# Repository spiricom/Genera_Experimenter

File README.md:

# Genera_H7_rev3
Genera repository for the rev3 boards (summer 2019) STM32H743
test

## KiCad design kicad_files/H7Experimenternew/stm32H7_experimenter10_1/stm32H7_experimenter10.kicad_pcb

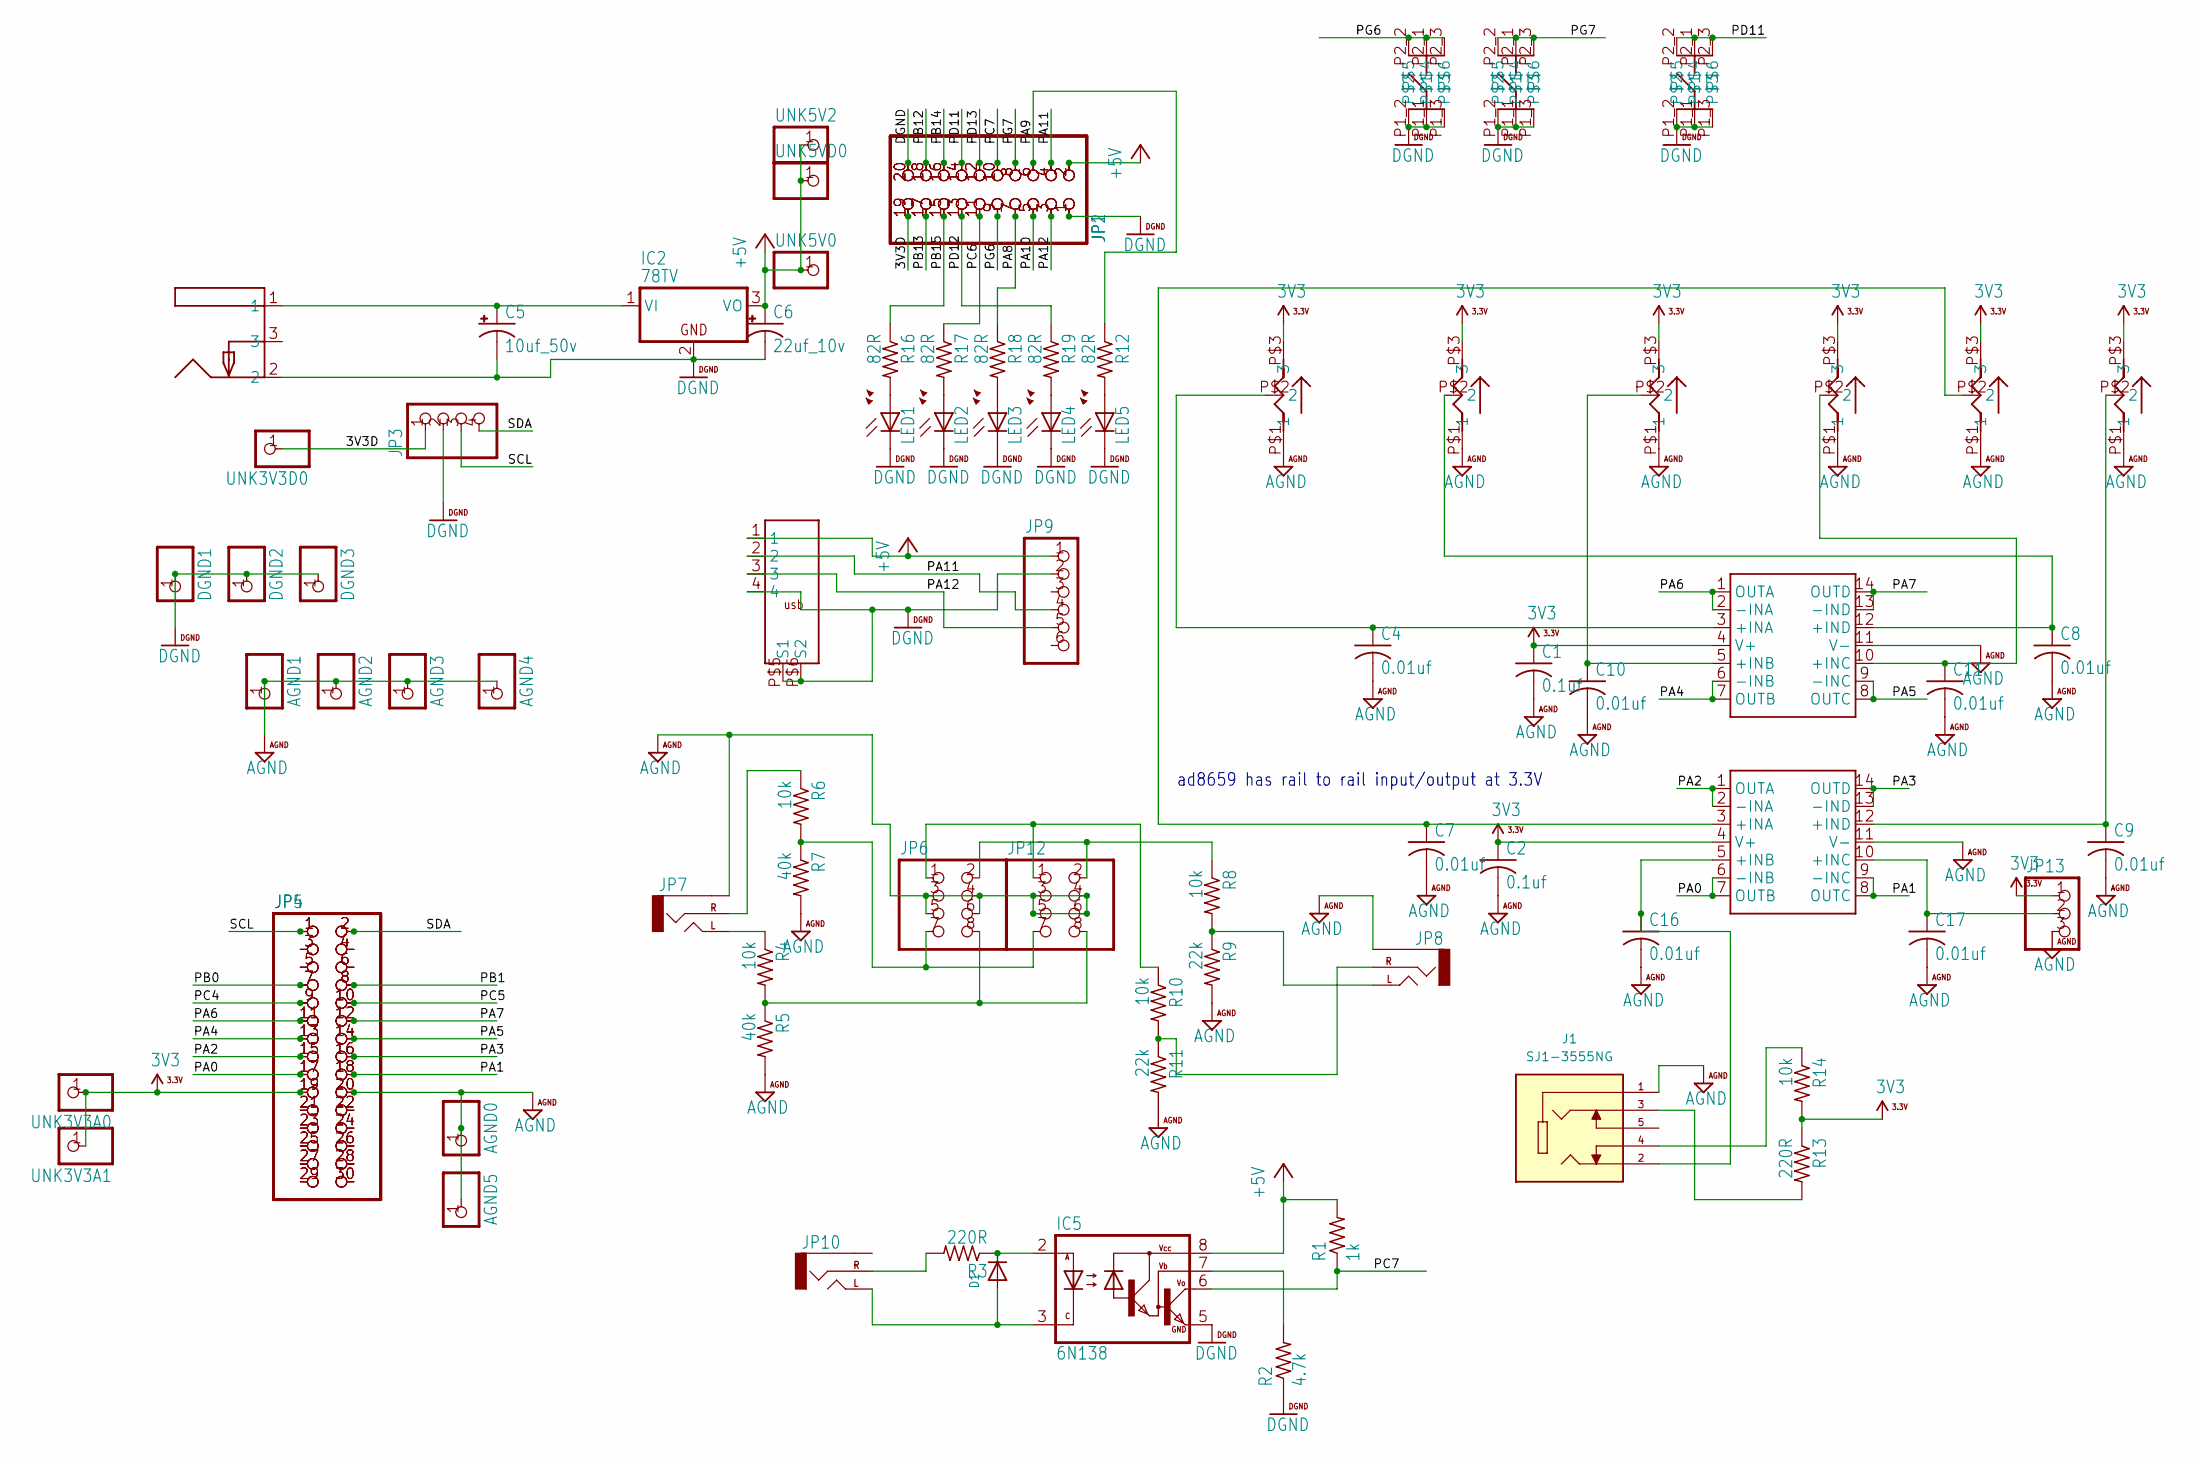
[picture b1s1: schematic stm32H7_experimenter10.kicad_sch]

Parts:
AGND0, AGND1, AGND2, AGND3, AGND4, AGND5: PINHD-1X1; 1X01; PARTNO *DNP
C1, C2: 0.1uf; C025-030X050; PARTNO K104K15X7RF5TL2
C4, C7, C8, C9, C10, C11, C16, C17: 0.01uf; C025-030X050; PARTNO K103K15X7RF5TL2
C5: 10uf_50v; SMC_C; PARTNO 293D106X9035C2TE3
C6: 22uf_10v; SMC_C; PARTNO T491C226K016AT
D1: DIODEDO-1N4148; DO-1N4148; PARTNO 1N4148
DGND1, DGND2, DGND3: PINHD-1X1; 1X01; PARTNO *DNP
IC1, IC3: AD8659; SO14; PARTNO AD8659ARZ-R7
IC2: 78TV; TO220V; PARTNO VX7805-1000
IC5: 6N138; DIL08; PARTNO 6N138
J1: SJ1-3555NG; CUI_SJ1-3555NG; PARTREV 1.05
JP1: PINHD-2X10; 2X10; PARTNO *DNP
JP2: PINHD-2X10; 2X10; PARTNO 67996-120HLF
JP3: PINHD-1X4; 1X04; PARTNO *DNP
JP4: PINHD-2X15; 2X15; PARTNO 67996-130HLF
JP5: PINHD-2X15; 2X15; PARTNO *DNP
JP6: PINHD-2X4; 2X04; PARTNO 67996-108HLF
JP7, JP8, JP10: AUDIO-JACKPTH; AUDIO-JACK; PARTNO SJ1-3525N
JP9: PINHD-1X6; 1X06
JP12: PINHD-2X4; 2X04; PARTNO *DNP
JP13: PINHD-1X3; 1X03; PARTNO *DNP
LED1, LED2, LED3, LED4, LED5: LED3MM; PARTNO 151031SS04000
P1, P2, P3, P4, P5, P6: RK09SONGHUEI; R0904N; PARTNO *
R1: 1k; 0204_5; PARTNO RNMF14FTC1K00
R2: 4.7k; 0204_5; PARTNO RNMF14FTC4K70
R3: 220R; 0204_5; PARTNO RNMF14FTC220R
R4, R6, R8, R10, R14: 10k; 0204_5; PARTNO RNMF14FTC10K0
R5, R7: 40k; 0204_5; PARTNO RNMF14FTC39K0
R9, R11: 22k; 0204_5; PARTNO RNMF14FTC22K0
R12, R18, R19: 82R; 0204_5; PARTNO RNMF14FTC82R0
R13: 220R; 0204_5; PARTNO RNMF14FTC10K0
R16, R17: 82R; 0204V; PARTNO RNMF14FTC82R0
S1, S2, S3: TL52_PLUS; PARTNO TL52AF160Q
U$1: PJ-058AH_PWR_JACK; PJ-058AH
U$3: USB_292303-1; 292303
UNK3V3A0, UNK3V3A1, UNK3V3D0, UNK5V0, UNK5V2, UNK5VD0: PINHD-1X1; 1X01; PARTNO *DNP

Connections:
3V3: C1.1, C2.1, IC1.4 (V+), IC3.4 (V+), JP4.19, JP5.19, JP13.1, P1.P$3 (3), P2.P$3 (3), P3.P$3 (3), P4.P$3 (3), P5.P$3 (3), P6.P$3 (3), R13.1, R14.2, UNK3V3A0.1, UNK3V3A1.1
+5V: C6.+, IC2.3 (VO), IC5.8 (VCC), JP1.2, JP2.2, JP9.1, R1.2, U$3.1, UNK5V0.1, UNK5V2.1, UNK5VD0.1
/3V3D: JP1.19, JP2.19, JP3.1, UNK3V3D0.1
/PA0: IC3.6 (-INB), IC3.7 (OUTB), JP4.17, JP5.17
/PA1: IC3.8 (OUTC), IC3.9 (-INC), JP4.18, JP5.18
/PA2: IC3.1 (OUTA), IC3.2 (-INA), JP4.15, JP5.15
/PA3: IC3.13 (-IND), IC3.14 (OUTD), JP4.16, JP5.16
/PA4: IC1.6 (-INB), IC1.7 (OUTB), JP4.13, JP5.13
/PA5: IC1.8 (OUTC), IC1.9 (-INC), JP4.14, JP5.14
/PA6: IC1.1 (OUTA), IC1.2 (-INA), JP4.11, JP5.11
/PA7: IC1.13 (-IND), IC1.14 (OUTD), JP4.12, JP5.12
/PA8: JP1.7, JP2.7, R18.1
/PA9: JP1.6, JP2.6, R12.1
/PA10: JP1.5, JP2.5
/PA11: JP1.4, JP2.4, JP9.4, U$3.2
/PA12: JP1.3, JP2.3, JP9.5, U$3.3
/PB0: JP4.7, JP5.7
/PB1: JP4.8, JP5.8
/PB12: JP1.18, JP2.18
/PB13: JP1.17, JP2.17
/PB14: JP1.16, JP2.16
/PB15: JP1.15, JP2.15, R16.1
/PC4: JP4.9, JP5.9
/PC5: JP4.10, JP5.10
/PC6: JP1.11, JP2.11, R17.1
/PC7: IC5.6 (VO), JP1.10, JP2.10, R1.1
/PD11: JP1.14, JP2.14, S3.P2_1, S3.P2_2, S3.P2_3
/PD12: JP1.13, JP2.13, R19.1
/PD13: JP1.12, JP2.12
/PG6: JP1.9, JP2.9, S1.P2_1, S1.P2_2, S1.P2_3
/PG7: JP1.8, JP2.8, S2.P2_1, S2.P2_2, S2.P2_3
/SCL: JP3.3, JP4.1, JP5.1
/SDA: JP3.4, JP4.2, JP5.2
AGND: AGND0.1, AGND1.1, AGND2.1, AGND3.1, AGND4.1, AGND5.1, C1.2, C2.2, C4.2, C7.2, C8.2, C9.2, C10.2, C11.2, C16.2, C17.2, IC1.11 (V-), IC3.11 (V-), J1.1, JP4.20, JP5.20, JP6.3, JP6.4, JP6.5, JP6.6, JP7.SLEEVE, JP8.SLEEVE, JP12.3, JP12.4, JP12.5, JP12.6, JP13.3, P1.P$1 (1), P2.P$1 (1), P3.P$1 (1), P4.P$1 (1), P5.P$1 (1), P6.P$1 (1), R5.2, R7.2, R9.2, R11.2
DGND: C5.-, C6.-, DGND1.1, DGND2.1, DGND3.1, IC2.2 (GND), IC5.5 (GND), JP1.1, JP1.20, JP2.1, JP2.20, JP3.2, JP9.2, LED1.K (C), LED2.K (C), LED3.K (C), LED4.K (C), LED5.K (C), R2.1, S1.P1_1, S1.P1_2, S1.P1_3, S2.P1_1, S2.P1_2, S2.P1_3, S3.P1_1, S3.P1_2, S3.P1_3, U$1.2, U$3.4, U$3.P$5 (S1), U$3.P$6 (S2)
unnamed: C4.1, IC1.3 (+INA), P1.P$2 (2)
unnamed: C10.1, IC1.5 (+INB), P3.P$2 (2)
unnamed: C11.1, IC1.10 (+INC), P4.P$2 (2)
unnamed: C8.1, IC1.12 (+IND), P2.P$2 (2)
unnamed: C5.+, IC2.1 (VI), U$1.1
unnamed: C7.1, IC3.3 (+INA), P5.P$2 (2)
unnamed: C16.1, IC3.5 (+INB), J1.2
unnamed: C17.1, IC3.10 (+INC), JP13.2
unnamed: C9.1, IC3.12 (+IND), P6.P$2 (2)
unnamed: D1.C, IC5.2 (A), R3.1
unnamed: D1.A, IC5.3 (C), JP10.TIP (LEFT)
unnamed: IC5.7 (VB), R2.2
unnamed: J1.3, R13.2
unnamed: J1.4, R14.1
unnamed: JP4.3, JP5.3
unnamed: JP4.4, JP5.4
unnamed: JP4.5, JP5.5
unnamed: JP4.6, JP5.6
unnamed: JP4.21, JP5.21
unnamed: JP4.22, JP5.22
unnamed: JP4.23, JP5.23
unnamed: JP4.24, JP5.24
unnamed: JP4.25, JP5.25
unnamed: JP4.26, JP5.26
unnamed: JP4.27, JP5.27
unnamed: JP4.28, JP5.28
unnamed: JP4.29, JP5.29
unnamed: JP4.30, JP5.30
unnamed: JP7.TIP (LEFT), R4.1
unnamed: JP7.RING (RIGHT), R6.1
unnamed: JP8.TIP (LEFT), R8.2, R9.1
unnamed: JP8.RING (RIGHT), R10.2, R11.1
unnamed: JP10.RING (RIGHT), R3.2
unnamed: JP6.1, JP12.1, R10.1
unnamed: JP6.2, JP12.2, R8.1
unnamed: JP6.7, JP12.7, R6.2, R7.1
unnamed: JP6.8, JP12.8, R4.2, R5.1
unnamed: LED1.A, R16.2
unnamed: LED2.A, R17.2
unnamed: LED3.A, R18.2
unnamed: LED4.A, R19.2
unnamed: LED5.A, R12.2

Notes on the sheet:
ad8659 has rail to rail input/output at 3.3V

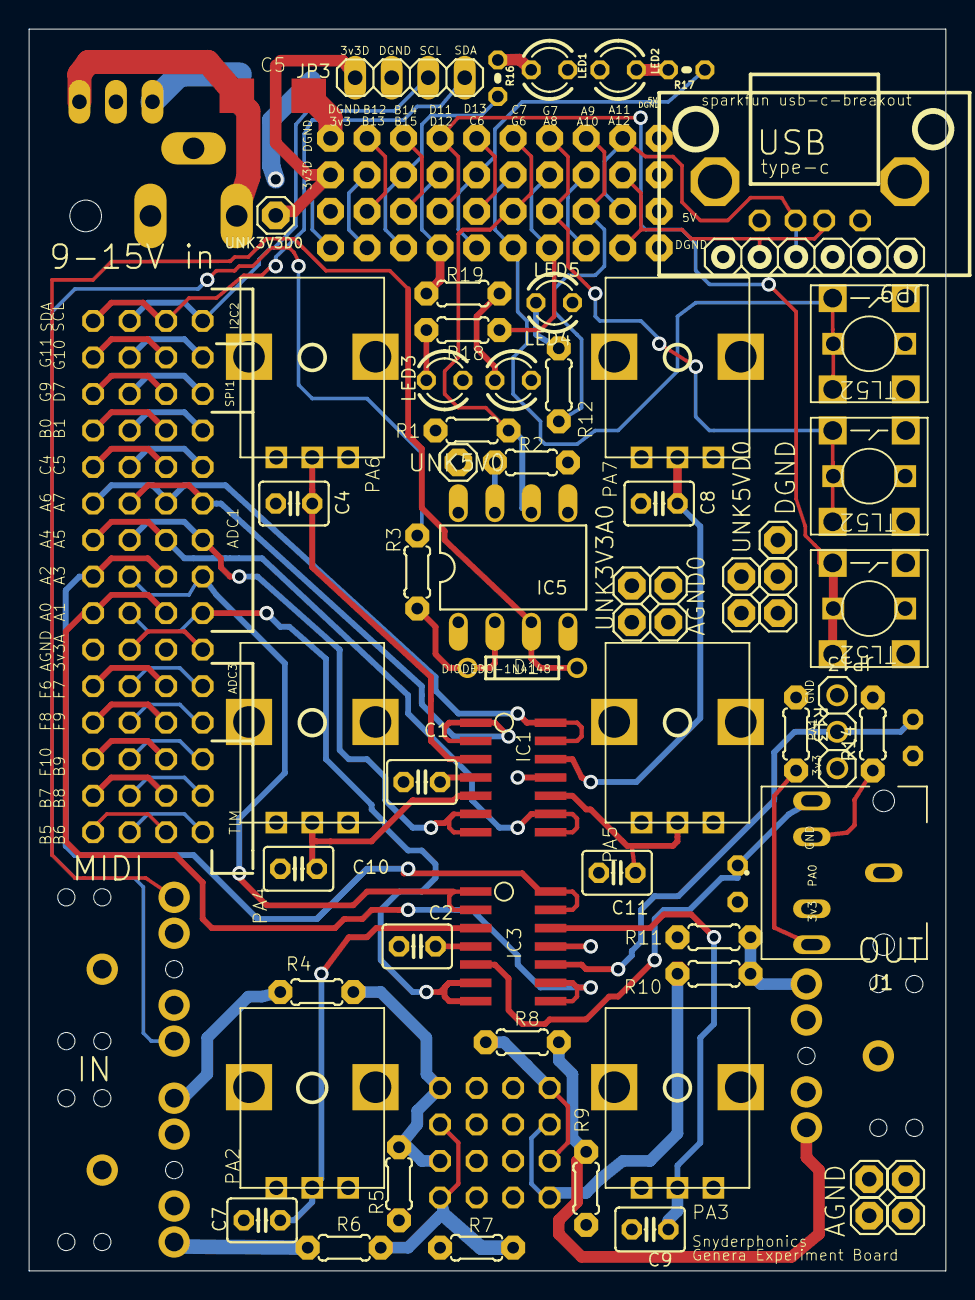
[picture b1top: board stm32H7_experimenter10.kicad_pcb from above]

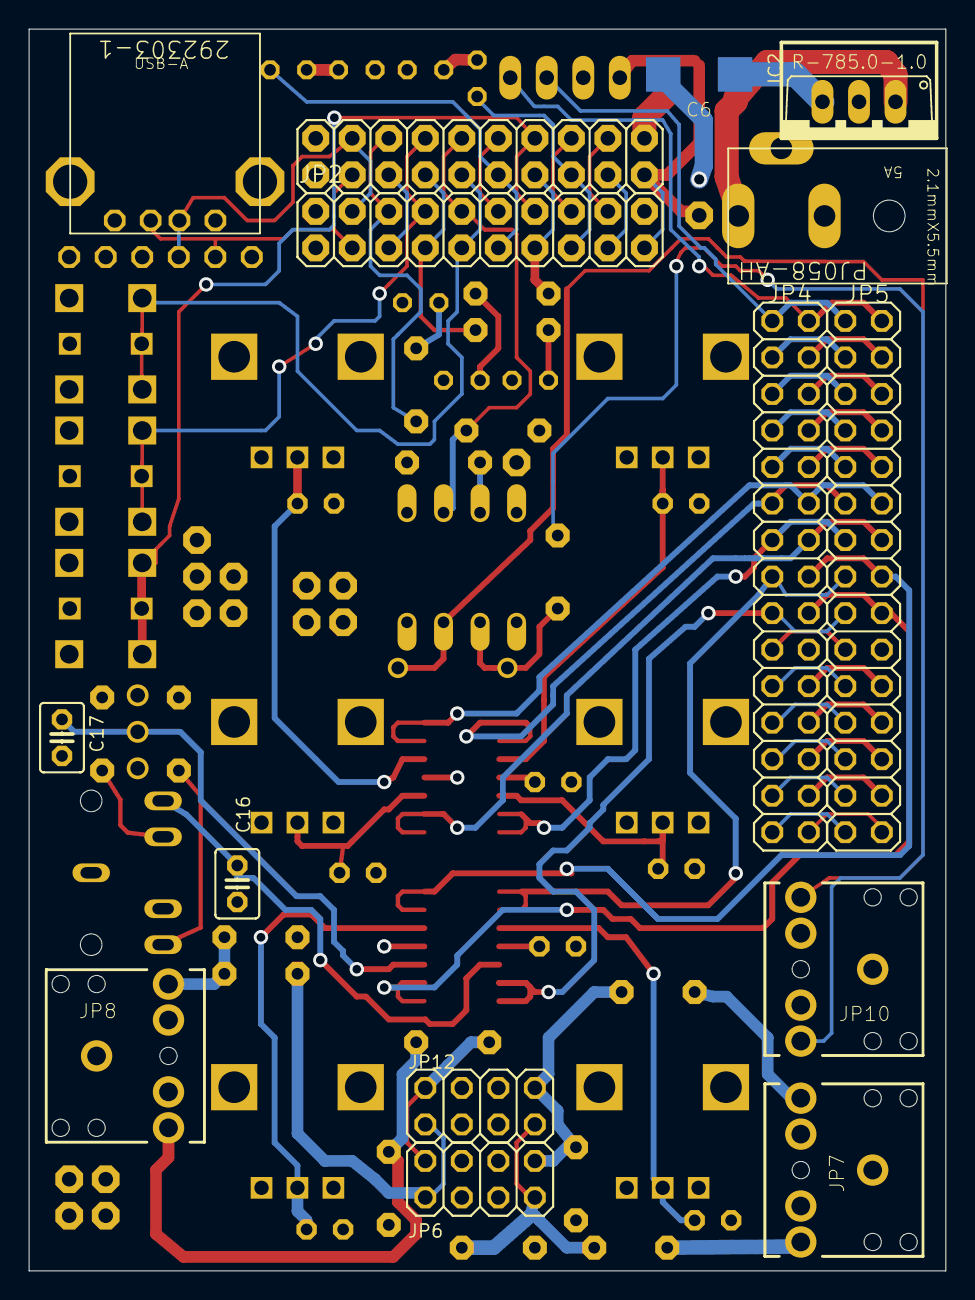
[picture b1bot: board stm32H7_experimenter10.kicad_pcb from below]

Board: 4 copper layers, 63.8 x 86.4 mm, 79 parts (15 on the bottom side), 77 nets.

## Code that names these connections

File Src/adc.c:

/* USER CODE BEGIN Header */
/**
  ******************************************************************************
  * @file    adc.c
  * @brief   This file provides code for the configuration
  *          of the ADC instances.
  ******************************************************************************
  * @attention
  *
  * Copyright (c) 2022 STMicroelectronics.
  * All rights reserved.
  *
  * This software is licensed under terms that can be found in the LICENSE file
  * in the root directory of this software component.
  * If no LICENSE file comes with this software, it is provided AS-IS.
  *
  ******************************************************************************
  */
/* USER CODE END Header */
/* Includes ------------------------------------------------------------------*/
#include "adc.h"

/* USER CODE BEGIN 0 */

/* USER CODE END 0 */

ADC_HandleTypeDef hadc1;
DMA_HandleTypeDef hdma_adc1;

/* ADC1 init function */
void MX_ADC1_Init(void)
{

  /* USER CODE BEGIN ADC1_Init 0 */

  /* USER CODE END ADC1_Init 0 */

  ADC_MultiModeTypeDef multimode = {0};
  ADC_ChannelConfTypeDef sConfig = {0};

  /* USER CODE BEGIN ADC1_Init 1 */

  /* USER CODE END ADC1_Init 1 */

  /** Common config
  */
  hadc1.Instance = ADC1;
  hadc1.Init.ClockPrescaler = ADC_CLOCK_ASYNC_DIV4;
  hadc1.Init.Resolution = ADC_RESOLUTION_16B;
  hadc1.Init.ScanConvMode = ADC_SCAN_ENABLE;
  hadc1.Init.EOCSelection = ADC_EOC_SEQ_CONV;
  hadc1.Init.LowPowerAutoWait = DISABLE;
  hadc1.Init.ContinuousConvMode = ENABLE;
  hadc1.Init.NbrOfConversion = 6;
  hadc1.Init.DiscontinuousConvMode = DISABLE;
  hadc1.Init.ExternalTrigConv = ADC_SOFTWARE_START;
  hadc1.Init.ExternalTrigConvEdge = ADC_EXTERNALTRIGCONVEDGE_NONE;
  hadc1.Init.ConversionDataManagement = ADC_CONVERSIONDATA_DMA_CIRCULAR;
  hadc1.Init.Overrun = ADC_OVR_DATA_PRESERVED;
  hadc1.Init.LeftBitShift = ADC_LEFTBITSHIFT_NONE;
  hadc1.Init.OversamplingMode = ENABLE;
  hadc1.Init.Oversampling.Ratio = 64;
  hadc1.Init.Oversampling.RightBitShift = ADC_RIGHTBITSHIFT_6;
  hadc1.Init.Oversampling.TriggeredMode = ADC_TRIGGEREDMODE_SINGLE_TRIGGER;
  hadc1.Init.Oversampling.OversamplingStopReset = ADC_REGOVERSAMPLING_CONTINUED_MODE;
  if (HAL_ADC_Init(&hadc1) != HAL_OK)
  {
    Error_Handler();
  }

  /** Configure the ADC multi-mode
  */
  multimode.Mode = ADC_MODE_INDEPENDENT;
  if (HAL_ADCEx_MultiModeConfigChannel(&hadc1, &multimode) != HAL_OK)
  {
    Error_Handler();
  }

  /** Configure Regular Channel
  */
  sConfig.Channel = ADC_CHANNEL_7;
  sConfig.Rank = ADC_REGULAR_RANK_1;
  sConfig.SamplingTime = ADC_SAMPLETIME_64CYCLES_5;
  sConfig.SingleDiff = ADC_SINGLE_ENDED;
  sConfig.OffsetNumber = ADC_OFFSET_NONE;
  sConfig.Offset = 0;
  sConfig.OffsetSignedSaturation = DISABLE;
  if (HAL_ADC_ConfigChannel(&hadc1, &sConfig) != HAL_OK)
  {
    Error_Handler();
  }

  /** Configure Regular Channel
  */
  sConfig.Channel = ADC_CHANNEL_3;
  sConfig.Rank = ADC_REGULAR_RANK_2;
  if (HAL_ADC_ConfigChannel(&hadc1, &sConfig) != HAL_OK)
  {
    Error_Handler();
  }

  /** Configure Regular Channel
  */
  sConfig.Channel = ADC_CHANNEL_19;
  sConfig.Rank = ADC_REGULAR_RANK_3;
  if (HAL_ADC_ConfigChannel(&hadc1, &sConfig) != HAL_OK)
  {
    Error_Handler();
  }

  /** Configure Regular Channel
  */
  sConfig.Channel = ADC_CHANNEL_18;
  sConfig.Rank = ADC_REGULAR_RANK_4;
  if (HAL_ADC_ConfigChannel(&hadc1, &sConfig) != HAL_OK)
  {
    Error_Handler();
  }

  /** Configure Regular Channel
  */
  sConfig.Channel = ADC_CHANNEL_15;
  sConfig.Rank = ADC_REGULAR_RANK_5;
  if (HAL_ADC_ConfigChannel(&hadc1, &sConfig) != HAL_OK)
  {
    Error_Handler();
  }

  /** Configure Regular Channel
  */
  sConfig.Channel = ADC_CHANNEL_14;
  sConfig.Rank = ADC_REGULAR_RANK_6;
  if (HAL_ADC_ConfigChannel(&hadc1, &sConfig) != HAL_OK)
  {
    Error_Handler();
  }
  /* USER CODE BEGIN ADC1_Init 2 */

  /* USER CODE END ADC1_Init 2 */

}

void HAL_ADC_MspInit(ADC_HandleTypeDef* adcHandle)
{

  GPIO_InitTypeDef GPIO_InitStruct = {0};
  HAL_DMA_MuxSyncConfigTypeDef pSyncConfig= {0};
  if(adcHandle->Instance==ADC1)
  {
  /* USER CODE BEGIN ADC1_MspInit 0 */

  /* USER CODE END ADC1_MspInit 0 */
    /* ADC1 clock enable */
    __HAL_RCC_ADC12_CLK_ENABLE();

    __HAL_RCC_GPIOA_CLK_ENABLE();
    /**ADC1 GPIO Configuration
    PA0     ------> ADC1_INP16
    PA1     ------> ADC1_INN16
    PA1     ------> ADC1_INP17
    PA2     ------> ADC1_INP14
    PA3     ------> ADC1_INP15
    PA4     ------> ADC1_INP18
    PA5     ------> ADC1_INP19
    PA6     ------> ADC1_INP3
    PA7     ------> ADC1_INP7
    */
    GPIO_InitStruct.Pin = GPIO_PIN_0|GPIO_PIN_1|GPIO_PIN_2|GPIO_PIN_3
                          |GPIO_PIN_4|GPIO_PIN_5|GPIO_PIN_6|GPIO_PIN_7;
    GPIO_InitStruct.Mode = GPIO_MODE_ANALOG;
    GPIO_InitStruct.Pull = GPIO_NOPULL;
    HAL_GPIO_Init(GPIOA, &GPIO_InitStruct);

    /* ADC1 DMA Init */
    /* ADC1 Init */
    hdma_adc1.Instance = DMA2_Stream0;
    hdma_adc1.Init.Request = DMA_REQUEST_ADC1;
    hdma_adc1.Init.Direction = DMA_PERIPH_TO_MEMORY;
    hdma_adc1.Init.PeriphInc = DMA_PINC_DISABLE;
    hdma_adc1.Init.MemInc = DMA_MINC_ENABLE;
    hdma_adc1.Init.PeriphDataAlignment = DMA_PDATAALIGN_HALFWORD;
    hdma_adc1.Init.MemDataAlignment = DMA_MDATAALIGN_HALFWORD;
    hdma_adc1.Init.Mode = DMA_CIRCULAR;
    hdma_adc1.Init.Priority = DMA_PRIORITY_HIGH;
    hdma_adc1.Init.FIFOMode = DMA_FIFOMODE_ENABLE;
    hdma_adc1.Init.FIFOThreshold = DMA_FIFO_THRESHOLD_1QUARTERFULL;
    hdma_adc1.Init.MemBurst = DMA_MBURST_SINGLE;
    hdma_adc1.Init.PeriphBurst = DMA_PBURST_SINGLE;
    if (HAL_DMA_Init(&hdma_adc1) != HAL_OK)
    {
      Error_Handler();
    }

    pSyncConfig.SyncSignalID = HAL_DMAMUX1_SYNC_EXTI0;
    pSyncConfig.SyncPolarity = HAL_DMAMUX_SYNC_RISING;
    pSyncConfig.SyncEnable = DISABLE;
    pSyncConfig.EventEnable = ENABLE;
    pSyncConfig.RequestNumber = 1;
    if (HAL_DMAEx_ConfigMuxSync(&hdma_adc1, &pSyncConfig) != HAL_OK)
    {
      Error_Handler();
    }

    __HAL_LINKDMA(adcHandle,DMA_Handle,hdma_adc1);

    /* ADC1 interrupt Init */
    HAL_NVIC_SetPriority(ADC_IRQn, 5, 0);
    HAL_NVIC_EnableIRQ(ADC_IRQn);
  /* USER CODE BEGIN ADC1_MspInit 1 */

  /* USER CODE END ADC1_MspInit 1 */
  }
}

void HAL_ADC_MspDeInit(ADC_HandleTypeDef* adcHandle)
{

  if(adcHandle->Instance==ADC1)
  {
  /* USER CODE BEGIN ADC1_MspDeInit 0 */

  /* USER CODE END ADC1_MspDeInit 0 */
    /* Peripheral clock disable */
    __HAL_RCC_ADC12_CLK_DISABLE();

    /**ADC1 GPIO Configuration
    PA0     ------> ADC1_INP16
    PA1     ------> ADC1_INN16
    PA1     ------> ADC1_INP17
    PA2     ------> ADC1_INP14
    PA3     ------> ADC1_INP15
    PA4     ------> ADC1_INP18
    PA5     ------> ADC1_INP19
    PA6     ------> ADC1_INP3
    PA7     ------> ADC1_INP7
    */
    HAL_GPIO_DeInit(GPIOA, GPIO_PIN_0|GPIO_PIN_1|GPIO_PIN_2|GPIO_PIN_3
                          |GPIO_PIN_4|GPIO_PIN_5|GPIO_PIN_6|GPIO_PIN_7);

    /* ADC1 DMA DeInit */
    HAL_DMA_DeInit(adcHandle->DMA_Handle);

    /* ADC1 interrupt Deinit */
    HAL_NVIC_DisableIRQ(ADC_IRQn);
  /* USER CODE BEGIN ADC1_MspDeInit 1 */

  /* USER CODE END ADC1_MspDeInit 1 */
  }
}

/* USER CODE BEGIN 1 */

/* USER CODE END 1 */

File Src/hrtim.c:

/* USER CODE BEGIN Header */
/**
  ******************************************************************************
  * @file    hrtim.c
  * @brief   This file provides code for the configuration
  *          of the HRTIM instances.
  ******************************************************************************
  * @attention
  *
  * Copyright (c) 2026 STMicroelectronics.
  * All rights reserved.
  *
  * This software is licensed under terms that can be found in the LICENSE file
  * in the root directory of this software component.
  * If no LICENSE file comes with this software, it is provided AS-IS.
  *
  ******************************************************************************
  */
/* USER CODE END Header */
/* Includes ------------------------------------------------------------------*/
#include "hrtim.h"

/* USER CODE BEGIN 0 */

/* USER CODE END 0 */

HRTIM_HandleTypeDef hhrtim;

/* HRTIM init function */
void MX_HRTIM_Init(void)
{

  /* USER CODE BEGIN HRTIM_Init 0 */

  /* USER CODE END HRTIM_Init 0 */

  HRTIM_TimeBaseCfgTypeDef pTimeBaseCfg = {0};
  HRTIM_SimplePWMChannelCfgTypeDef pSimplePWMChannelCfg = {0};

  /* USER CODE BEGIN HRTIM_Init 1 */

  /* USER CODE END HRTIM_Init 1 */
  hhrtim.Instance = HRTIM1;
  hhrtim.Init.HRTIMInterruptResquests = HRTIM_IT_NONE;
  hhrtim.Init.SyncOptions = HRTIM_SYNCOPTION_NONE;
  if (HAL_HRTIM_Init(&hhrtim) != HAL_OK)
  {
    Error_Handler();
  }
  pTimeBaseCfg.Period = 0x3fff;
  pTimeBaseCfg.RepetitionCounter = 0x00;
  pTimeBaseCfg.PrescalerRatio = HRTIM_PRESCALERRATIO_DIV1;
  pTimeBaseCfg.Mode = HRTIM_MODE_CONTINUOUS;
  if (HAL_HRTIM_TimeBaseConfig(&hhrtim, HRTIM_TIMERINDEX_TIMER_B, &pTimeBaseCfg) != HAL_OK)
  {
    Error_Handler();
  }
  pSimplePWMChannelCfg.Pulse = 0x7ff;
  pSimplePWMChannelCfg.Polarity = HRTIM_OUTPUTPOLARITY_HIGH;
  pSimplePWMChannelCfg.IdleLevel = HRTIM_OUTPUTIDLELEVEL_INACTIVE;
  if (HAL_HRTIM_SimplePWMChannelConfig(&hhrtim, HRTIM_TIMERINDEX_TIMER_B, HRTIM_OUTPUT_TB2, &pSimplePWMChannelCfg) != HAL_OK)
  {
    Error_Handler();
  }
  if (HAL_HRTIM_TimeBaseConfig(&hhrtim, HRTIM_TIMERINDEX_TIMER_C, &pTimeBaseCfg) != HAL_OK)
  {
    Error_Handler();
  }
  if (HAL_HRTIM_SimplePWMChannelConfig(&hhrtim, HRTIM_TIMERINDEX_TIMER_C, HRTIM_OUTPUT_TC1, &pSimplePWMChannelCfg) != HAL_OK)
  {
    Error_Handler();
  }
  if (HAL_HRTIM_SimplePWMChannelConfig(&hhrtim, HRTIM_TIMERINDEX_TIMER_C, HRTIM_OUTPUT_TC2, &pSimplePWMChannelCfg) != HAL_OK)
  {
    Error_Handler();
  }
  if (HAL_HRTIM_TimeBaseConfig(&hhrtim, HRTIM_TIMERINDEX_TIMER_D, &pTimeBaseCfg) != HAL_OK)
  {
    Error_Handler();
  }
  if (HAL_HRTIM_SimplePWMChannelConfig(&hhrtim, HRTIM_TIMERINDEX_TIMER_D, HRTIM_OUTPUT_TD1, &pSimplePWMChannelCfg) != HAL_OK)
  {
    Error_Handler();
  }
  if (HAL_HRTIM_SimplePWMChannelConfig(&hhrtim, HRTIM_TIMERINDEX_TIMER_D, HRTIM_OUTPUT_TD2, &pSimplePWMChannelCfg) != HAL_OK)
  {
    Error_Handler();
  }
  if (HAL_HRTIM_TimeBaseConfig(&hhrtim, HRTIM_TIMERINDEX_TIMER_E, &pTimeBaseCfg) != HAL_OK)
  {
    Error_Handler();
  }
  if (HAL_HRTIM_SimplePWMChannelConfig(&hhrtim, HRTIM_TIMERINDEX_TIMER_E, HRTIM_OUTPUT_TE2, &pSimplePWMChannelCfg) != HAL_OK)
  {
    Error_Handler();
  }
  /* USER CODE BEGIN HRTIM_Init 2 */

  /* USER CODE END HRTIM_Init 2 */
  HAL_HRTIM_MspPostInit(&hhrtim);

}

void HAL_HRTIM_MspInit(HRTIM_HandleTypeDef* hrtimHandle)
{

  RCC_PeriphCLKInitTypeDef PeriphClkInitStruct = {0};
  if(hrtimHandle->Instance==HRTIM1)
  {
  /* USER CODE BEGIN HRTIM1_MspInit 0 */

  /* USER CODE END HRTIM1_MspInit 0 */

  /** Initializes the peripherals clock
  */
    PeriphClkInitStruct.PeriphClockSelection = RCC_PERIPHCLK_HRTIM1;
    PeriphClkInitStruct.Hrtim1ClockSelection = RCC_HRTIM1CLK_CPUCLK;
    if (HAL_RCCEx_PeriphCLKConfig(&PeriphClkInitStruct) != HAL_OK)
    {
      Error_Handler();
    }

    /* HRTIM1 clock enable */
    __HAL_RCC_HRTIM1_CLK_ENABLE();
  /* USER CODE BEGIN HRTIM1_MspInit 1 */

  /* USER CODE END HRTIM1_MspInit 1 */
  }
}

void HAL_HRTIM_MspPostInit(HRTIM_HandleTypeDef* hrtimHandle)
{

  GPIO_InitTypeDef GPIO_InitStruct = {0};
  if(hrtimHandle->Instance==HRTIM1)
  {
  /* USER CODE BEGIN HRTIM1_MspPostInit 0 */

  /* USER CODE END HRTIM1_MspPostInit 0 */

    __HAL_RCC_GPIOG_CLK_ENABLE();
    __HAL_RCC_GPIOA_CLK_ENABLE();
    /**HRTIM GPIO Configuration
    PG7     ------> HRTIM_CHE2
    PA8     ------> HRTIM_CHB2
    PA9     ------> HRTIM_CHC1
    PA10     ------> HRTIM_CHC2
    PA11     ------> HRTIM_CHD1
    PA12     ------> HRTIM_CHD2
    */
    GPIO_InitStruct.Pin = GPIO_PIN_7;
    GPIO_InitStruct.Mode = GPIO_MODE_AF_PP;
    GPIO_InitStruct.Pull = GPIO_NOPULL;
    GPIO_InitStruct.Speed = GPIO_SPEED_FREQ_LOW;
    GPIO_InitStruct.Alternate = GPIO_AF2_HRTIM1;
    HAL_GPIO_Init(GPIOG, &GPIO_InitStruct);

    GPIO_InitStruct.Pin = GPIO_PIN_8|GPIO_PIN_9|GPIO_PIN_10|GPIO_PIN_11
                          |GPIO_PIN_12;
    GPIO_InitStruct.Mode = GPIO_MODE_AF_PP;
    GPIO_InitStruct.Pull = GPIO_NOPULL;
    GPIO_InitStruct.Speed = GPIO_SPEED_FREQ_LOW;
    GPIO_InitStruct.Alternate = GPIO_AF2_HRTIM1;
    HAL_GPIO_Init(GPIOA, &GPIO_InitStruct);

  /* USER CODE BEGIN HRTIM1_MspPostInit 1 */

  /* USER CODE END HRTIM1_MspPostInit 1 */
  }

}

void HAL_HRTIM_MspDeInit(HRTIM_HandleTypeDef* hrtimHandle)
{

  if(hrtimHandle->Instance==HRTIM1)
  {
  /* USER CODE BEGIN HRTIM1_MspDeInit 0 */

  /* USER CODE END HRTIM1_MspDeInit 0 */
    /* Peripheral clock disable */
    __HAL_RCC_HRTIM1_CLK_DISABLE();
  /* USER CODE BEGIN HRTIM1_MspDeInit 1 */

  /* USER CODE END HRTIM1_MspDeInit 1 */
  }
}

/* USER CODE BEGIN 1 */

/* USER CODE END 1 */

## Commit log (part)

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2020-02-20 updating
2020-03-07 fixed issues with build and broken sw4stm config file
2020-03-07 added mempools to example
2020-03-07 fixed linker file to allow for SDRAM access
2020-03-21 added SPI
2020-03-22 removed unnecessary HAL peripherals, added string fret measurements roughly
2020-03-24 working electrobass makes sound but needs better attack detection
2020-03-26 working attack detector
2020-03-26 slight tweak to reduce mistriggers
2020-04-20 electrobass update;
2020-04-20 added usb midi functionality"
2020-04-23 added vadim zavalishin filters to have high and low shelf, and also saturation
2020-04-23 finished mackie-style eq example using the new Vadim Zavalashin filters. It works! Overloads when boosting highs, but thats probably because the source is white noise with more energy in the upper fr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
2020-04-23 filter test example
2020-06-20 got 3 ADC input channels syncronized with audio frame and samples. They can be used as audio inputs without distortion
2020-06-21 working example that detects which sensor was closest to strike based on oversampled time difference
2020-06-23 migrated to cubeide
2020-06-23 migrated to cubeide and fixed some things
2020-06-25 testing
2020-07-09 edited lots of things, somewht working pluck detection in adc callback, simple monophonic handling
2020-07-10 decent attack detection, currently trying to work on logging to SD card
2020-07-11 got data logging working up to about 50000 bytes. Need to extend beyond that by buffering and sending in chunks or by using SDRAM as temporary storage.
2020-07-27 code to record full sensor data from the electrobass and store it to an SD card for analysis
2020-08-25 updating electrobass
2020-08-30 simple distortion 192k
2020-08-31 distortion 192k example
2020-08-31 cleaned up cycle counter cruft
2020-08-31 updated code to reflect new LEAF changes
2020-08-31 added comment to explain interface;
2020-08-31 newer version with 2X oversampling of all saturation and no saturation in filters
2020-08-31 adjusted ranges of controls for better filtering
2020-08-31 moved comment
2020-09-01 version of filterbank
2020-09-02 pushing current version
2020-09-03 working version that reads a file named s.wav from SD card and plays it back looping.
2020-09-06 added code to allow parsing of broadcast wav files, which previously broke it. Still havent figured out how to handle multichannel files on the reading end
2020-09-06 fixed wave.c to properly read stereo files and read much more quickly by using a large scratch buffer and loading the whole sample data at once rather than tons of tiny sd card reads
2020-09-08 version where the genera takes two triggers in on the audio inputs and sends out two different samples on the output channels
2020-09-09 trying IDMA version of sdmmc
2020-09-10 quite good sample playback happening. Tested using SDMMC IDMA and it was slower because I couldnt use DTCMRAM. Went back to polling. Found tricky bug in the tSampler object that also explains weirdne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
2020-09-10 updated leaf
2020-09-11 added angies code as a leaf object, tested and working with pluck detection but not tested using amplitude information
2020-09-12 working electrobass
2020-11-15 current SD card code
2026-04-15 current state
2026-04-15 updated hal
2026-04-15 replaced with Electrosteel audio version
2026-04-15 errors during build but has electrosteel code
2026-06-11 Fixed bug, updated LEAF
    yeah
2026-06-11 test
2026-06-11 Small bugfix, added .gitignore
    changed uint to uint32_t for newer C versions
2026-06-11 Updated to new LEAF version
2026-06-11 attempted to add submodule reference to new leaf
2026-06-11 Better .gitignore attempt
2026-06-11 removed settings in gitignore
2026-06-11 more gitignore fixes
2026-06-11 More .gitignore fixes
2026-06-11 another
2026-06-11 final gitignore fix?
2026-06-11 another one
2026-06-11 unignoring .cproject
    Seems removing the .cproject file to get rid of the file directory reference to my own computer was a bad idea.
    Changed the leaf submodule directory to reference the workspace instead of my C drive, which should make it universal.
2026-06-11 One more undo
    Removed settings from the .gitignore.
    Not sure if the settings folder is auto-generated upon opening a project, or how system-specific the settings are.
2026-06-18 added kicad file
